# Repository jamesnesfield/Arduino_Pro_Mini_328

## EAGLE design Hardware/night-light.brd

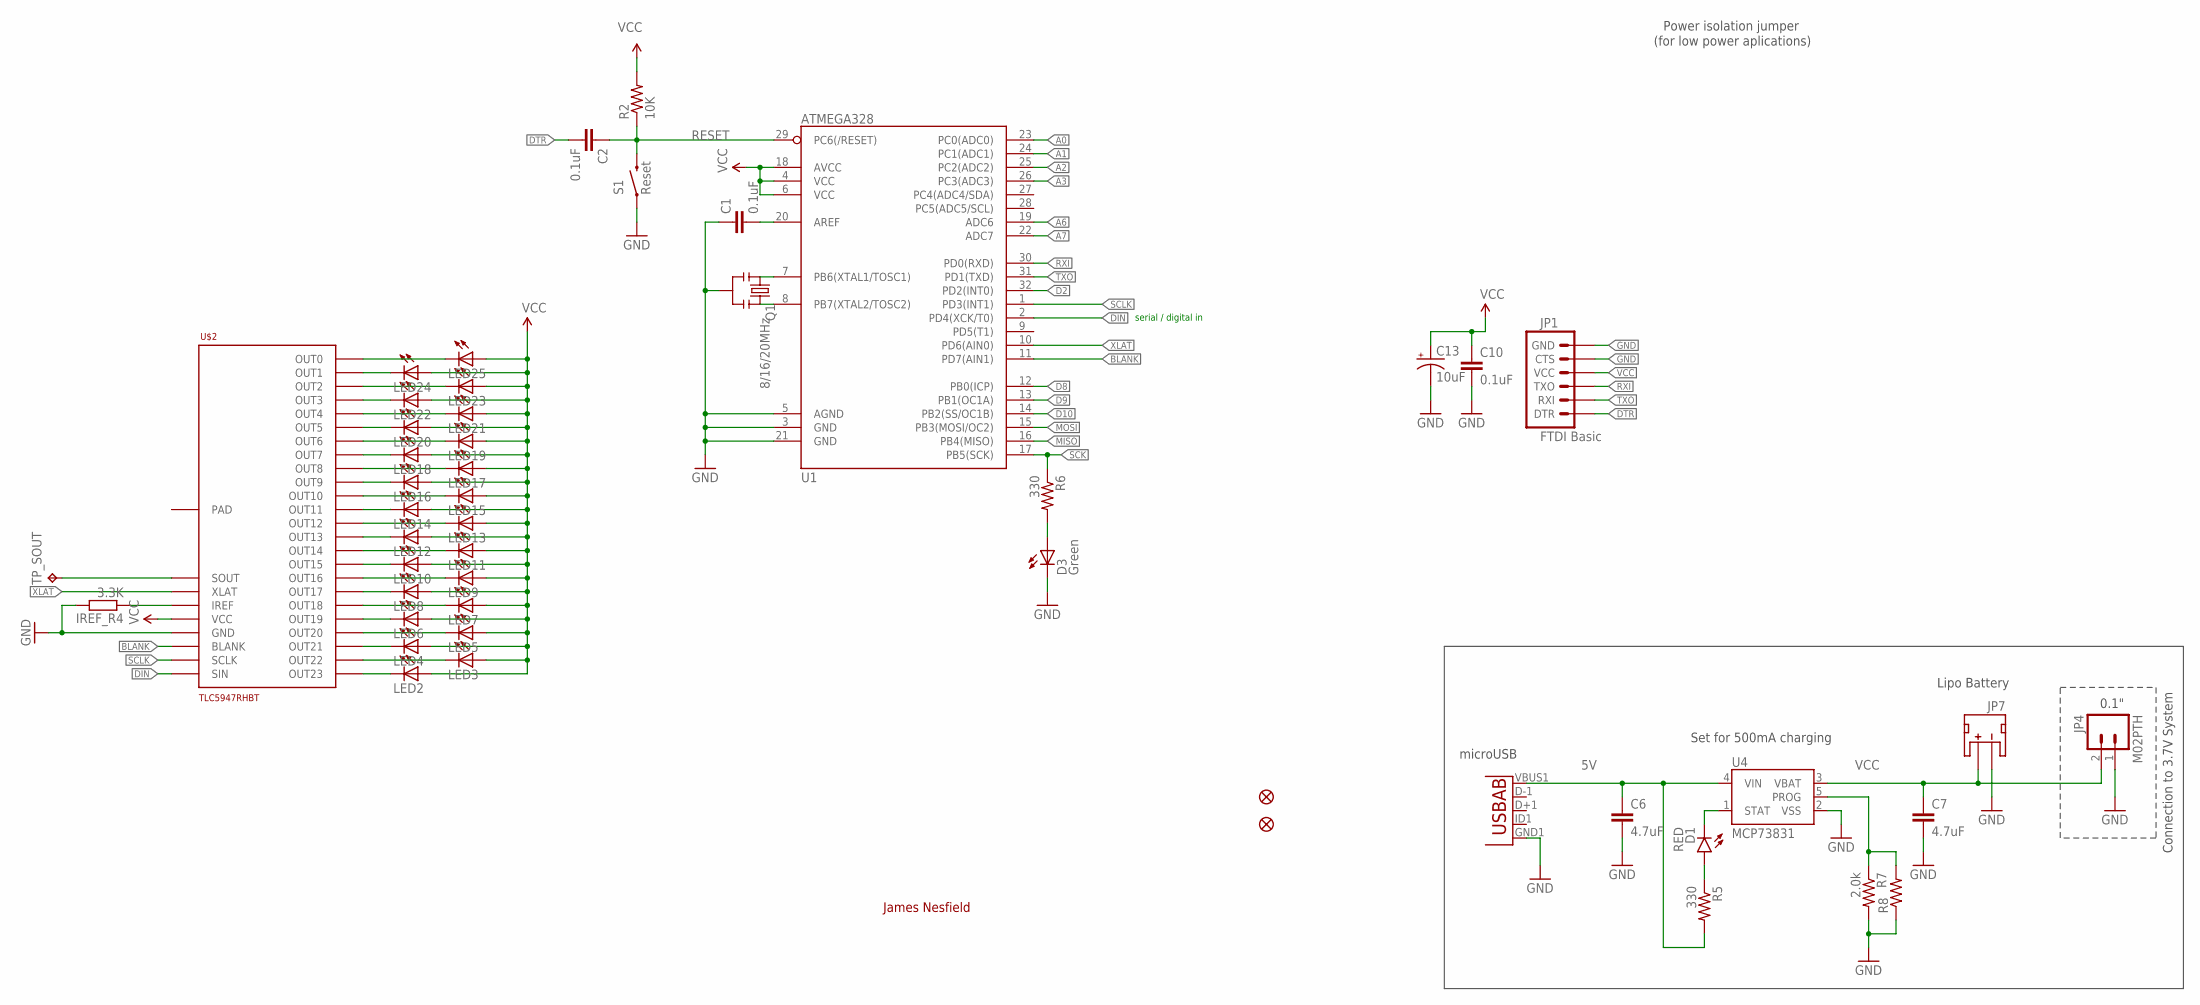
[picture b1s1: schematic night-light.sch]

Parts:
C1, C2, C10: 0.1uF; 0603-CAP
C6, C7: 4.7uF; 0603-CAP
C13: 10uF; EIA3216
D1: RED; LED-0603
D3: Green; 0603-LED-ALT1
IREF_R4: 3.3K; R0603
JP1: FTDI Basic; 1X06
JP4: M02PTH; 1X02
JP5, JP8: FIDUCIALUFIDUCIAL; MICRO-FIDUCIAL
JP6: Micro USB; USB-AB-MICRO-SMD_V03
JP7: JST; JST-2-SMD
LED2, LED3, LED4, LED5, LED6, LED7, LED8, LED9, LED10, LED11, LED12, LED13, LED14, LED15, LED16, LED17, LED18, LED19, LED20, LED21, LED22, LED23, LED24, LED25: LED_E; LED_1206
Q1: 8/16/20MHz; RESONATOR-SMD-1:1
R2: 10K; 0603-RES
R5, R6: 330; 0603-RES
R7: 2.0k; 0603-RES
R8: RESISTORPTH-1/4W-VERT-KIT; AXIAL-0.1EZ
S1: Reset; TACTILE-SWITCH-SMD-ALT01
TP_SOUT: TPTP20R; TP20R
U1: ATMEGA328; TQFP32-08
U4: MCP73831; SOT23-5
U$2: TLC5947RHBT; QFN32

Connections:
3.3V: LED2.A, LED3.A, LED4.A, LED5.A, LED6.A, LED7.A, LED8.A, LED9.A, LED10.A, LED11.A, LED12.A, LED13.A, LED14.A, LED15.A, LED16.A, LED17.A, LED18.A, LED19.A, LED20.A, LED21.A, LED22.A, LED23.A, LED24.A, LED25.A, U$2.28 (VCC)
5V: C6.1, JP6.VBUS1 (VBUS), R5.2, U4.4 (VIN)
A0: U1.23 (PC0(ADC0))
A1: U1.24 (PC1(ADC1))
A2: U1.25 (PC2(ADC2))
A3: U1.26 (PC3(ADC3))
A6: U1.19 (ADC6)
A7: U1.22 (ADC7)
BLANK: U1.11 (PD7(AIN1)), U$2.30 (BLANK)
D2: U1.32 (PD2(INT0))
D8: U1.12 (PB0(ICP))
D9: U1.13 (PB1(OC1A))
D10: U1.14 (PB2(SS/OC1B))
DIN: U1.2 (PD4(XCK/T0)), U$2.32 (SIN)
DTR: C2.2, JP1.1 (DTR)
GND: C1.1, C6.2, C7.2, C10.2, C13.C (-), D3.C, IREF_R4.2, JP1.5 (CTS), JP1.6 (GND), JP4.1, JP6.GND1 (GND), JP7.1 (-), Q1.2, R7.2, R8.P$1 (1), S1.1, S1.2 (1), U1.3 (GND), U1.5 (AGND), U1.21 (GND), U4.2 (VSS), U$2.29 (GND)
MISO: U1.16 (PB4(MISO))
MOSI: U1.15 (PB3(MOSI/OC2))
unnamed: Q1.3, U1.8 (PB7(XTAL2/TOSC2))
unnamed: Q1.1, U1.7 (PB6(XTAL1/TOSC1))
unnamed: LED25.C, U$2.1 (OUT0)
unnamed: IREF_R4.1, U$2.27 (IREF)
unnamed: D3.A, R6.2
unnamed: LED24.C, U$2.2 (OUT1)
unnamed: TP_SOUT.TP, U$2.25 (SOUT)
unnamed: LED23.C, U$2.3 (OUT2)
unnamed: LED22.C, U$2.4 (OUT3)
unnamed: LED21.C, U$2.5 (OUT4)
unnamed: LED20.C, U$2.6 (OUT5)
unnamed: LED19.C, U$2.7 (OUT6)
unnamed: LED18.C, U$2.8 (OUT7)
unnamed: LED17.C, U$2.9 (OUT8)
unnamed: LED16.C, U$2.10 (OUT9)
unnamed: LED15.C, U$2.11 (OUT10)
unnamed: LED14.C, U$2.12 (OUT11)
unnamed: LED13.C, U$2.13 (OUT12)
unnamed: LED12.C, U$2.14 (OUT13)
unnamed: LED11.C, U$2.15 (OUT14)
unnamed: LED10.C, U$2.16 (OUT15)
unnamed: LED9.C, U$2.17 (OUT16)
unnamed: LED8.C, U$2.18 (OUT17)
unnamed: LED7.C, U$2.19 (OUT18)
unnamed: LED6.C, U$2.20 (OUT19)
unnamed: LED5.C, U$2.21 (OUT20)
unnamed: LED4.C, U$2.22 (OUT21)
unnamed: LED3.C, U$2.23 (OUT22)
unnamed: LED2.C, U$2.24 (OUT23)
unnamed: C1.2, U1.20 (AREF)
unnamed: D1.A, R5.1
PROG1: R7.1, R8.P$2 (2), U4.5 (PROG)
RESET: C2.1, R2.1, S1.3 (2), S1.4 (2), U1.29 (PC6(/RESET))
RXI: JP1.3 (TXO), U1.30 (PD0(RXD))
SCK: R6.1, U1.17 (PB5(SCK))
SCLK: U1.1 (PD3(INT1)), U$2.31 (SCLK)
STAT1: D1.C, U4.1 (STAT)
TXO: JP1.2 (RXI), U1.31 (PD1(TXD))
VCC: C7.1, C10.1, C13.A (+), JP1.4 (VCC), JP4.2, JP7.2 (+), R2.2, U1.4 (VCC), U1.6 (VCC), U1.18 (AVCC), U4.3 (VBAT)
XLAT: U1.10 (PD6(AIN0)), U$2.26 (XLAT)

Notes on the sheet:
Power isolation jumper
(for low power aplications)
James Nesfield
serial / digital in
Set for 500mA charging
Connection to 3.7V System
0.1"
microUSB
Lipo Battery

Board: 2 copper layers, 50 parts (0 on the bottom side), 46 nets, no tracks yet.

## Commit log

2018-12-16 added tlc5947
2018-12-16 new pcb

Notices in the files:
parts and their libraries:
SparkFun-Capacitors: Licensing: Creative Commons ShareAlike 4.0 International - https://creativecommons.org/licenses/by-sa/4.0
